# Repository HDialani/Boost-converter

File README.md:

# Boost Converter 

I had access to a boost converter, so why not abuse it. The basic of boost converter explains what a boost converter is for people that don't know. The rest of the project assumes you know what a boost converter is and how it works

- [:heavy_check_mark:] Basics_of_boost_converter
- [ ] Components_Selection
- [ ] Controls
- [:heavy_check_mark: ] Current_Sensor
- [ ] EMI
- [ ] Inductor_Design
- [ ] PCB_Design
- [ ] Resources
- [ ] Switching_behavior
- [ ] Thermal
- [ ] Tools

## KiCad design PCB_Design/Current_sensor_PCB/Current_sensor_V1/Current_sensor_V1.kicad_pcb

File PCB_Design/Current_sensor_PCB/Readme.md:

# Read me

The V1 model is the one that was made by uni, but I converted it from Altium to Kicad.

# V1 design
The image below is the Schematic for V1 current PCB design

The image below is the routing for V1 current PCB design

The image below is a 3D model for V1 current PCB design

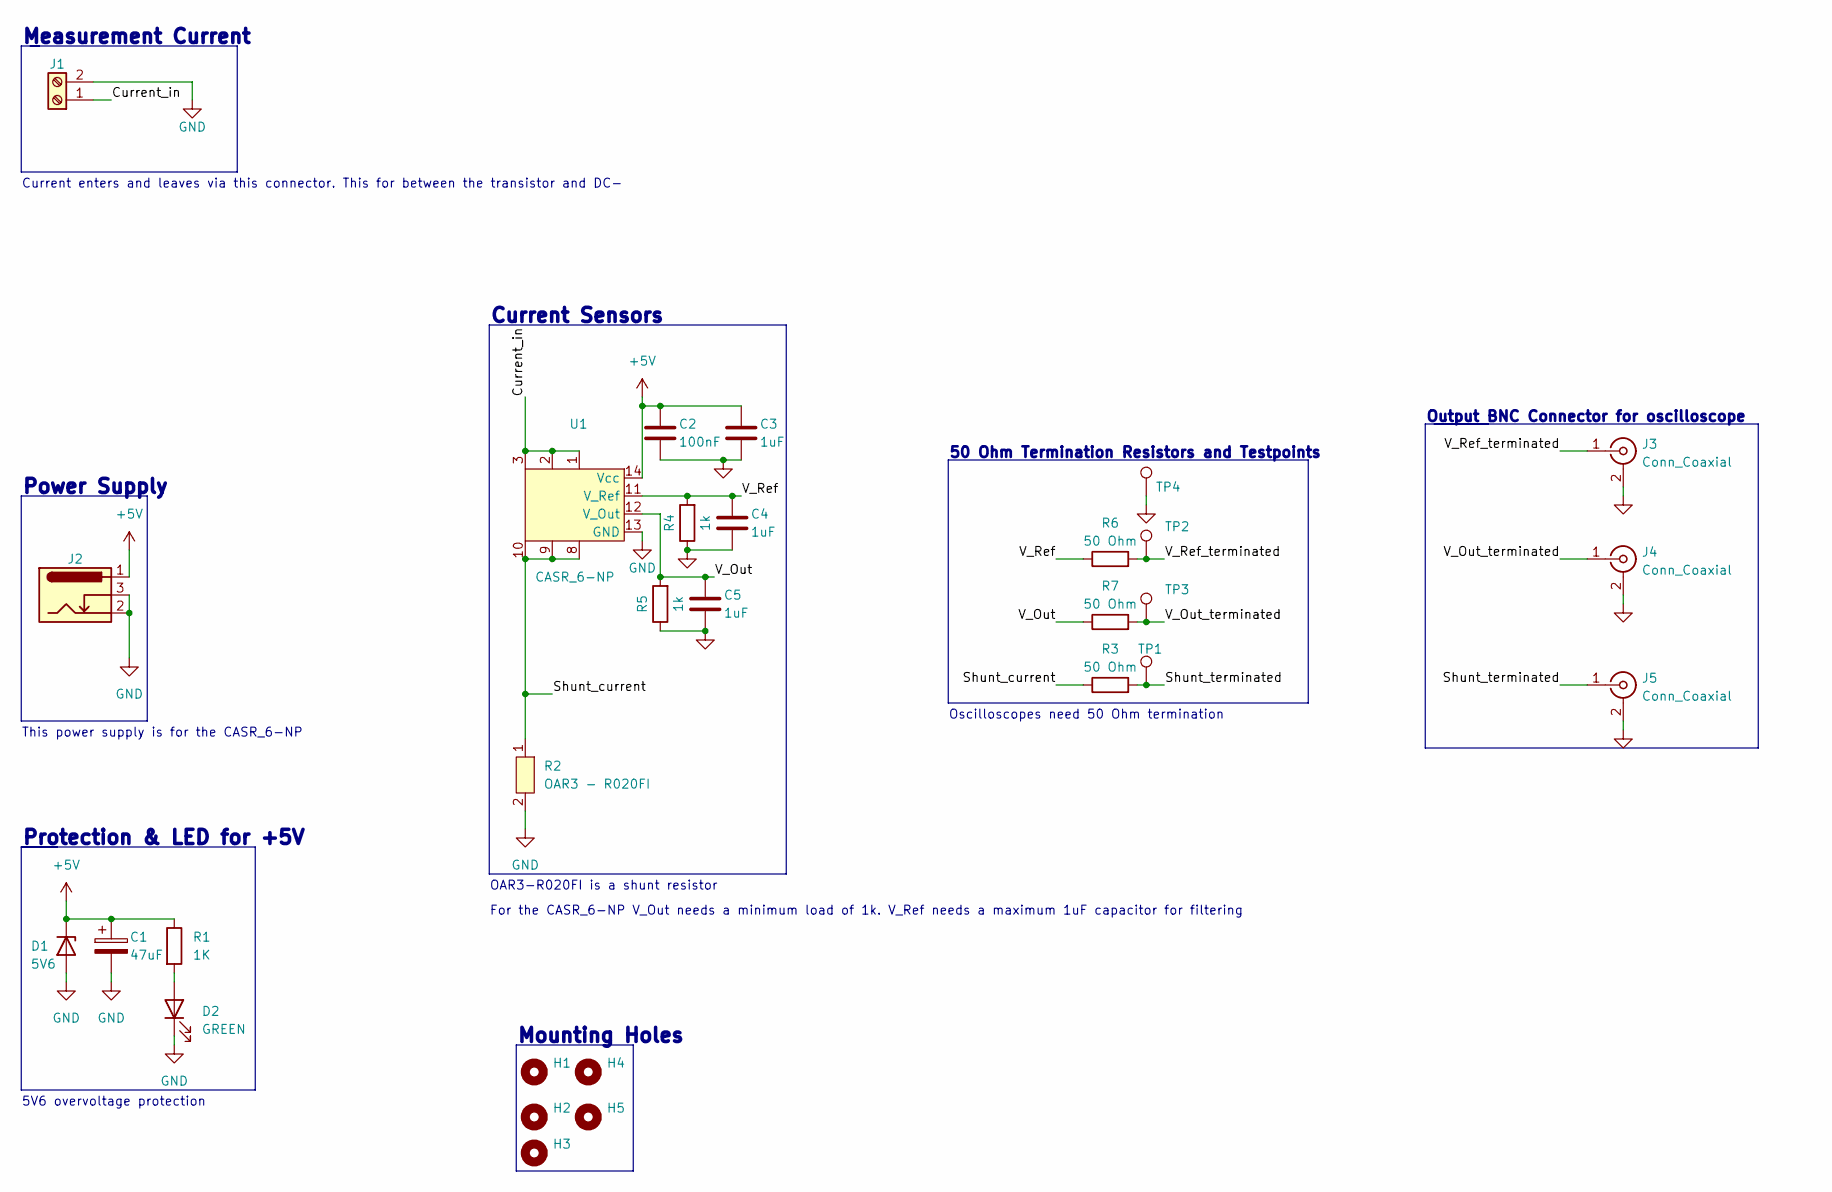
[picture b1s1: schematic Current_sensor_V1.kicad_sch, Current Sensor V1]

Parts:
C1: 47uF; CP_Elec_8x6.2
C2: 100nF; C_1206_3216Metric
C3, C4, C5: 1uF; C_1206_3216Metric
D1: 5V6; D_SMA
D2: GREEN; D_1206_3216Metric
H1, H2, H3, H4, H5: MountingHole; MountingHole_3.2mm_M3
J1: 284512-2; 2_pin_terminal_block_socket
J2: Barrel_Jack_Switch; BarrelJack_CLIFF_FC681465S_SMT_Horizontal
J3, J4, J5: Conn_Coaxial; BNC_TEConnectivity_1478204_Vertical
R1: 1K; R_1206_3216Metric
R2: OAR3 - R020FI; Shunt_Resistor
R3, R6, R7: 50 Ohm; R_1206_3216Metric
R4, R5: 1k; R_1206_3216Metric
TP1, TP2, TP3, TP4: TestPoint; TestPoint_Loop_D2.50mm_Drill1.0mm
U1: CASR_6-NP; CASR6NP

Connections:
+5V: C1.1, C2.1, C3.1, D1.1 (K), J2.1, R1.1, U1.14 (Vcc)
/Current_in: J1.1, U1.1, U1.2, U1.3
/Shunt_current: R2.1, R3.1, U1.8, U1.9, U1.10
/Shunt_terminated: J5.1 (In), R3.2, TP1.1
/V_Out: C5.1, R5.2, R7.1, U1.12 (V_Out)
/V_Out_terminated: J4.1 (In), R7.2, TP3.1
/V_Ref: C4.1, R4.2, R6.1, U1.11 (V_Ref)
/V_Ref_terminated: J3.1 (In), R6.2, TP2.1
GND: C1.2, C2.2, C3.2, C4.2, C5.2, D1.2 (A), D2.1 (K), J1.2, J2.2, J2.3, J3.2 (Ext), J4.2 (Ext), J5.2 (Ext), R2.2, R4.1, R5.1, TP4.1, U1.13 (GND)
unnamed: D2.2 (A), R1.2

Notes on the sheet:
Protection & LED for +5V
50 Ohm Termination Resistors and Testpoints
Power Supply
Mounting Holes
For the CASR_6-NP V_Out needs a minimum load of 1k. V_Ref needs a maximum 1uF capacitor for filtering
Measurement Current
5V6 overvoltage protection
Current Sensors
OAR3-R020FI is a shunt resistor
Oscilloscopes need 50 Ohm termination
Current enters and leaves via this connector. This for between the transistor and DC-
This power supply is for the CASR_6-NP
Output BNC Connector for oscilloscope

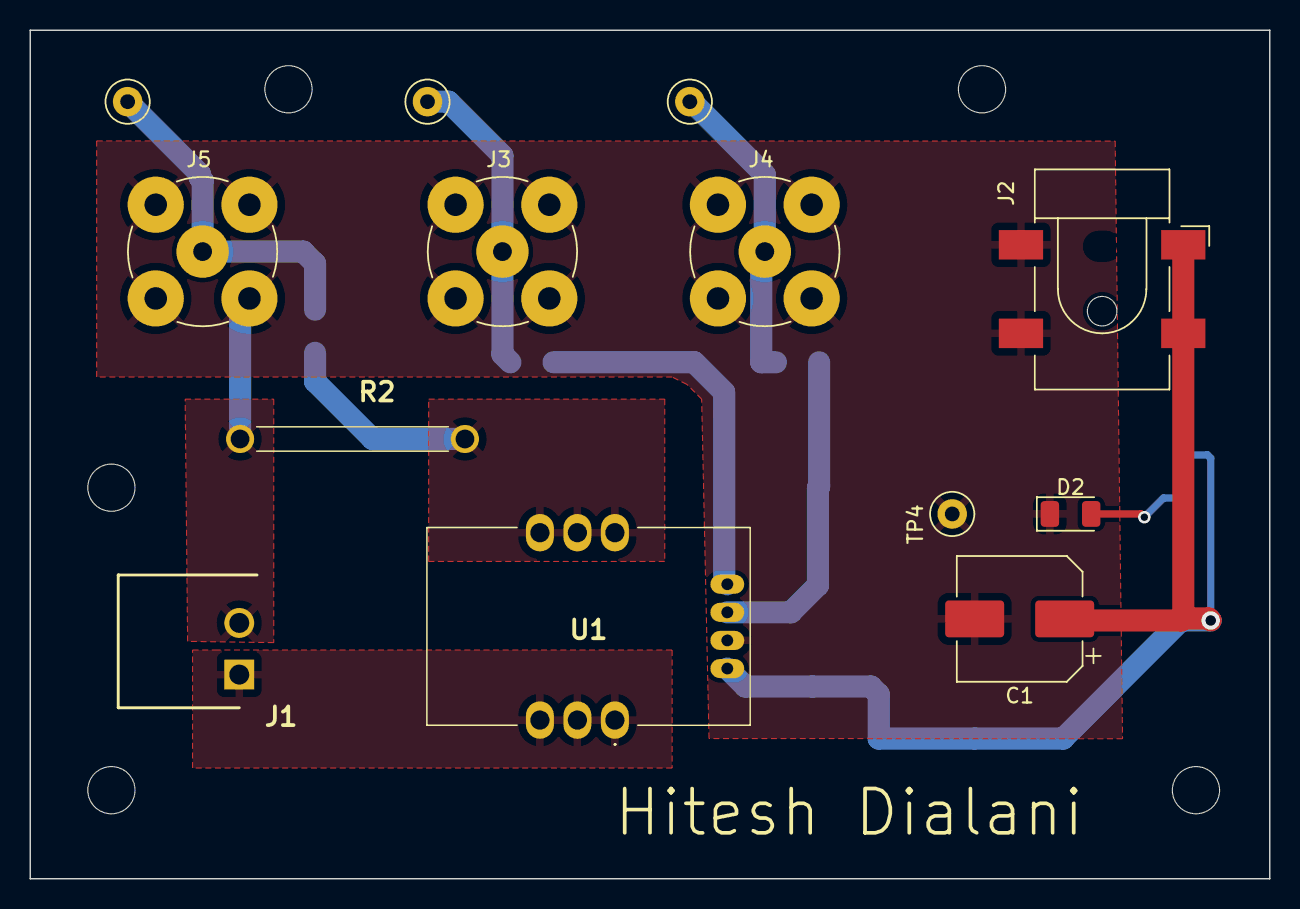
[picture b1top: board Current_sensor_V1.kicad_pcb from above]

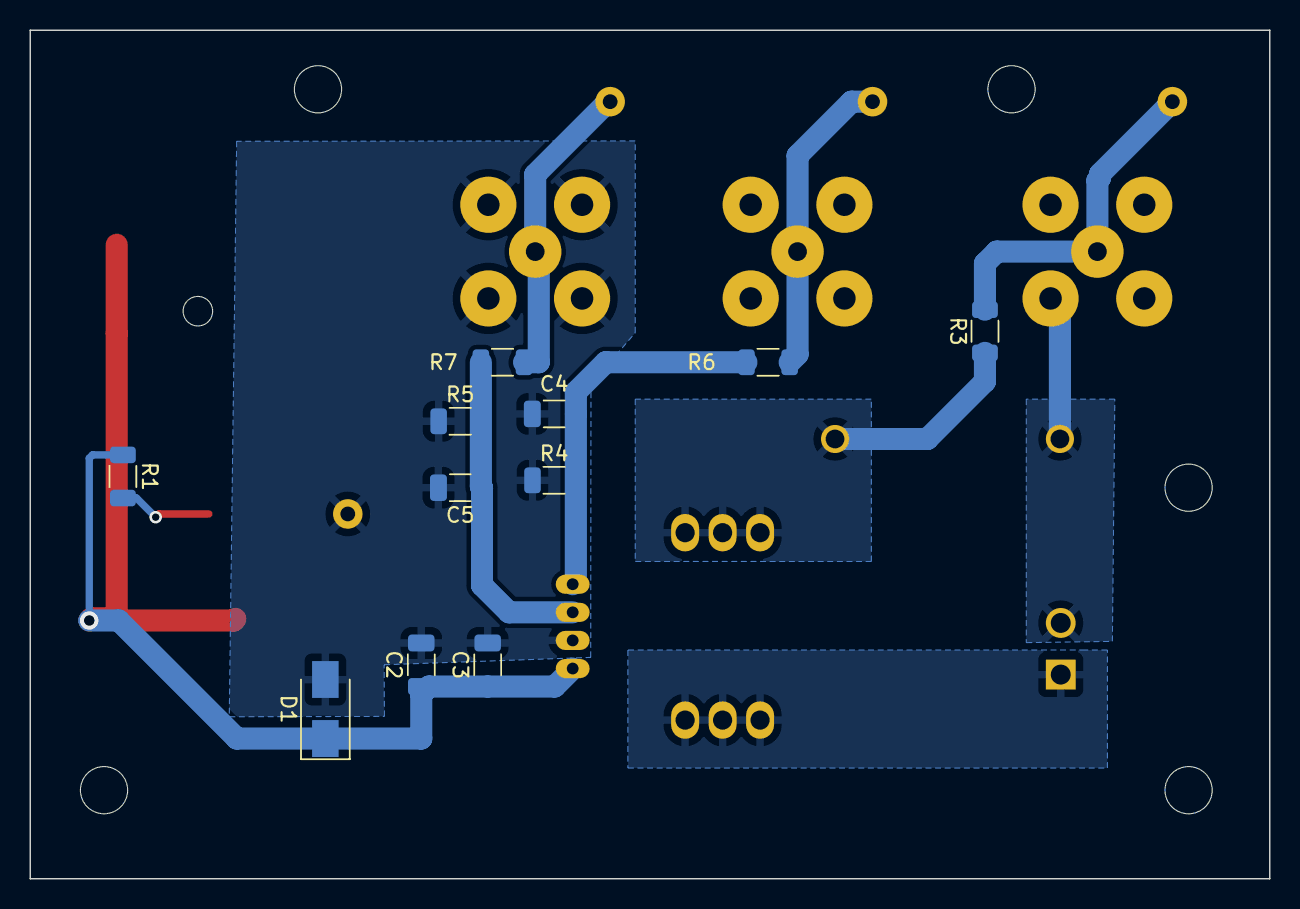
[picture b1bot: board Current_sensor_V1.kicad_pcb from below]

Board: 2 copper layers, 84.0 x 57.5 mm, 29 parts (11 on the bottom side), 10 nets.

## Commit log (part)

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2022-05-20 Added equations for CCM and DCM
2022-05-20 Ghetto image resolution fix
2022-06-03 inductor code
2022-06-04 A lot of code
2022-06-09 fixed CCM code and added IGBT option for Inductor code
2022-06-26 code for DCM
2022-06-26 forgot to change some parameters from MOSFET to IGBT
2022-08-05 Add files via upload
    please work
2022-08-09 modified inductor paramater code
2022-08-17 Python code for RLC step response
2022-08-17 help
2022-08-19 Fixed inverter LTspice model
2022-08-20 fixed LTspice for inverter model
2022-08-20 remove extra images
2022-08-20 Fixed images in nicer folders
2022-08-24 Starting point for thermal code
2022-08-24 Jupiter notebook version of Readme for controls
2022-08-24 measured temp
2022-08-24 more examples for cap LTSpice model
2022-08-25 Openloop Simulink Model
2022-08-25 Added resistor load temp in temp code
2022-08-25 update openloop Simulink code neatness
2022-08-25 nicer code
2022-08-26 Jupiter notebook code for Basics of Boost
2022-08-26 Jupiter notebook for Switching behaviour
2022-08-26 Make the Thermal python code nicer
2022-08-26 Current Sensor jupyternotebook
2022-08-28 Update current sensor jupiter notebook
2022-08-28 A bit of DCM Code for basics of boost
2022-08-28 Finished DCM code for Basics of Boost converter
2022-08-29 a bit of PI tuning
2022-08-30 fixed openloop dashboard, was f*cking standoffs
2022-08-30 A bit on DCM
2022-08-30 A bit on basics of boost
2022-08-30 A bit basics of boost
2022-08-31 Cleaned up Basic if boost jupyternotebook a bit
2022-08-31 Simulink code
2022-08-31 Basic of boost some speach on power supplies
2022-09-01 Control hell
2022-09-02 a bit on CCM part in Basics of Boost
2022-09-02 Finally fixed the CCM mode figure not working in Pycharm
2022-09-03 Schematic for Current sensor V1 is done
2022-09-03 Started on Micro-controller PC
2022-09-03 Made Footprint and placed everything in the correct spot for Current V1
2022-09-03 DCM graphs in basic of boost code
2022-09-04 Finished Current sensor V1 PCB
2022-09-04 Pics of PCB Current sensor V1
2022-09-04 Finished Page 1 of Micro controller schematic page
2022-09-04 Made some jupyter notebook writing
2022-09-05 IGBT Closed loop simulink model works
2022-09-05 Finished Basics of Boost
2022-09-06 The solution for the Serial configuration mouse problem is removing the chokes on the usb wire....
2022-09-06 Started on Inductor design jupyter notebook code
2022-09-06 Inductor design Jupyter notebook modifications
2022-09-06 Started on EMI jupyter notebook
2022-09-06 Some magic
2022-09-06 Added duty cycle all operation mode code in the code folder
2022-09-07 Some more text
2022-09-07 Some text for control implementation
2022-09-07 Some text on implemeation of controls notebook
2022-09-08 Nicer graphs for implementation of contols
2022-09-09 Cleaner fake boost model and code
2022-09-09 Added Closed loop explanation for implemtation jupyternotebook
2022-09-09 More text for implementation notebook
2022-09-09 Some order to the chaos
2022-09-09 Some more discription for Implementation notebook
2022-09-11 A beginning to components selection notebook
2022-09-12 Added duty cycle portion to implementation notebook
